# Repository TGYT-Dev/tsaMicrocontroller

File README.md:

a wearable project for TSA microcontroller project

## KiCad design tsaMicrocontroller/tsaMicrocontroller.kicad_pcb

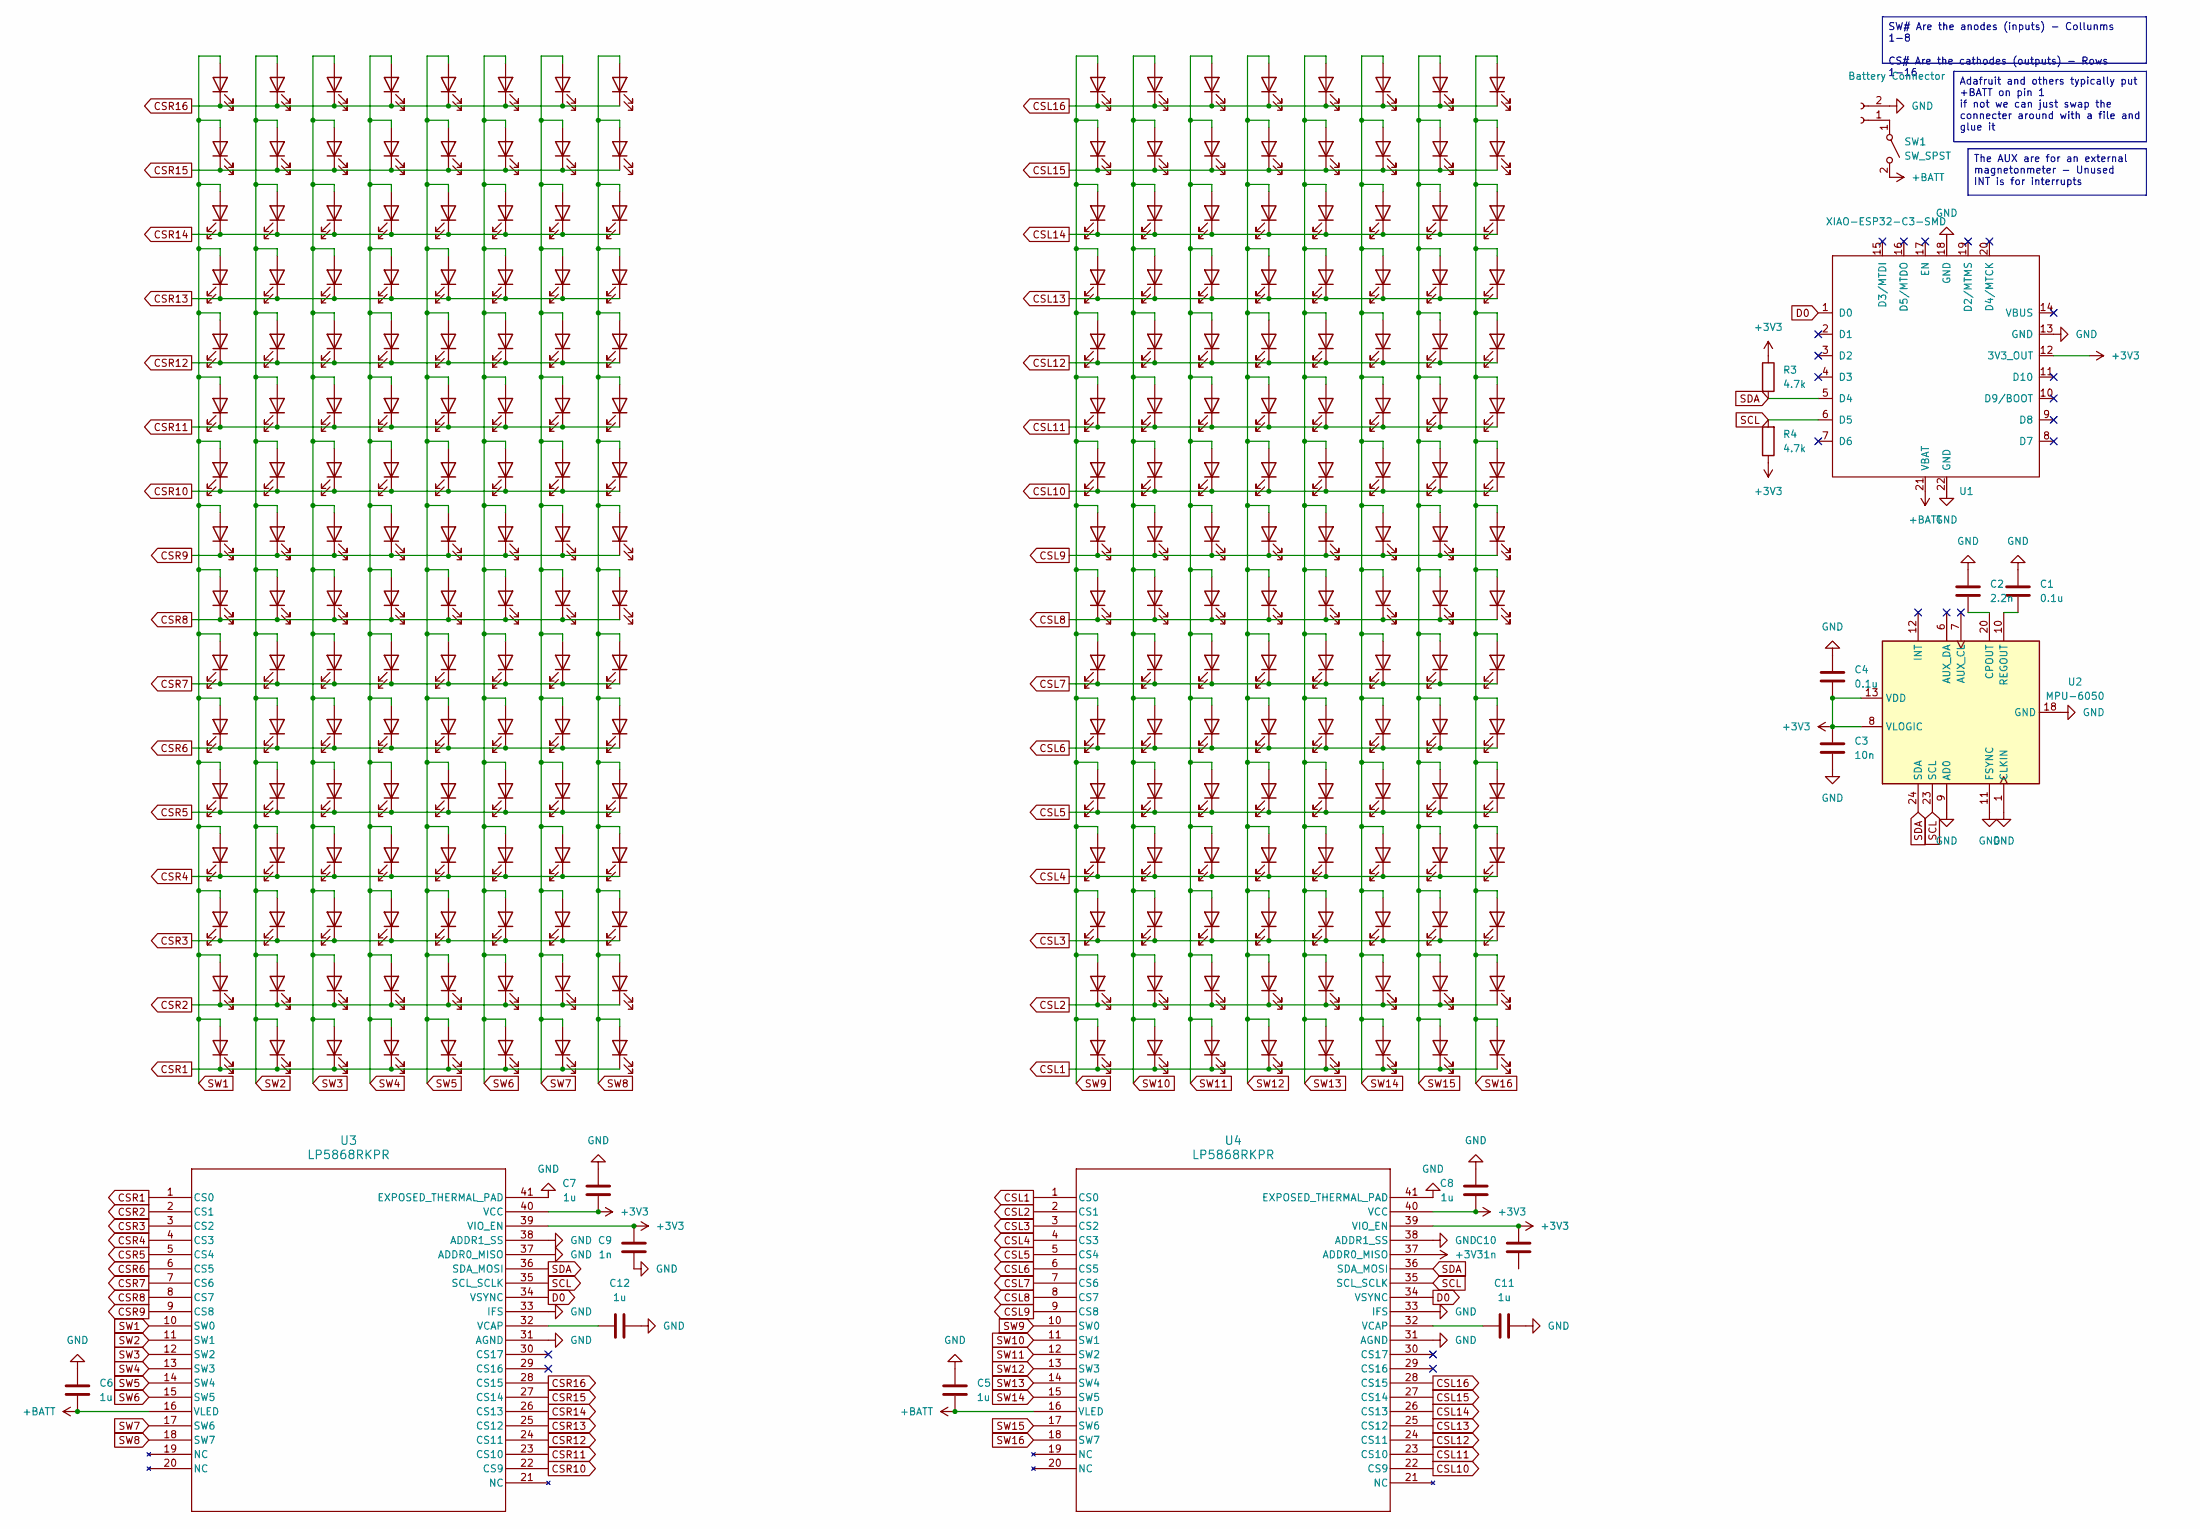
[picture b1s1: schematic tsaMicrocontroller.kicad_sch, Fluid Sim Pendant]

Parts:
C1, C4: 0.1u; C_01005_0402Metric
C2: 2.2n; C_01005_0402Metric
C3: 10n; C_01005_0402Metric
C5, C6, C7, C8, C11, C12: 1u; C_01005_0402Metric
C9, C10: 1n; C_01005_0402Metric
D146, D147, D148, D149, D150, D151, D152, D153, D154, D155, D156, D157, D158, D159, D160, D161, D162, D163, D164, D165, D166, D167, D168, D169, D170, D171, D172, D173, D174, D175, D176, D177, D178, D179, D180, D181, D182, D183, D184, D185, D186, D187, D188, D189, D190, D191, D192, D193, D194, D195, D196, D197, D198, D199, D200, D201, D202, D203, D204, D205, D206, D207, D208, D209, D210, D211, D212, D213, D214, D215, D216, D217, D218, D219, D220, D221, D222, D223, D224, D225, D226, D227, D228, D229, D230, D231, D232, D233, D234, D235, D236, D237, D238, D239, D240, D241, D242, D243, D244, D245, D246, D247, D248, D249, D250, D251, D252, D253, D254, D255, D256, D257, D258, D259, D260, D261, D262, D263, D264, D265, D266, D267, D268, D269, D270, D271, D272, D273, D274, D275, D276, D277, D278, D279, D280, D281, D282, D283, D284, D285, D286, D287, D288, D289, D290, D291, D292, D293, D294, D295, D296, D297, D298, D299, D300, D301, D302, D303, D304, D305, D306, D307, D308, D309, D310, D311, D312, D313, D314, D315, D316, D317, D318, D319, D320, D321, D322, D323, D324, D325, D326, D327, D328, D329, D330, D331, D332, D333, D334, D335, D336, D337, D338, D339, D340, D341, D342, D343, D344, D345, D346, D347, D348, D349, D350, D351, D352, D353, D354, D355, D356, D357, D358, D359, D360, D361, D362, D363, D364, D365, D366, D367, D368, D369, D370, D371, D372, D373, D374, D375, D376, D377, D378, D379, D380, D381, D382, D383, D384, D385, D386, D387, D388, D389, D390, D391, D392, D393, D394, D395, D396, D397, D398, D399, D400, D401: LED
J1: Battery Connector; JST_PH_S2B-PH-K_1x02_P2.00mm_Horizontal
R3, R4: 4.7k; R_0201_0603Metric_Pad0.64x0.40mm_HandSolder
SW1: SW_SPST; SW_DIP_SPSTx01_Slide_6.7x4.1mm_W6.73mm_P2.54mm_LowProfile_J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
U1: XIAO-ESP32-C3-SMD; MCU_Seeed_ESP32C3
U2: MPU-6050; InvenSense_QFN-24_4x4mm_P0.5mm
U3, U4: LP5868RKPR; VQFN40-RKP_TEX

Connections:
+3V3: C3.1, C4.2, C7.2, C8.2, C9.2, C10.2, R3.1, R4.1, U1.12 (3V3_OUT), U2.8 (VLOGIC), U2.13 (VDD), U3.39 (VIO_EN), U3.40 (VCC), U4.37 (ADDR0_MISO), U4.39 (VIO_EN), U4.40 (VCC)
+BATT: C5.2, C6.2, SW1.2 (B), U1.21 (VBAT), U3.16 (VLED), U4.16 (VLED)
CSL1: D279.1 (K), D301.1 (K), D321.1 (K), D337.1 (K), D353.1 (K), D369.1 (K), D385.1 (K), D401.1 (K), U4.1 (CS0)
CSL2: D276.1 (K), D300.1 (K), D320.1 (K), D336.1 (K), D352.1 (K), D368.1 (K), D384.1 (K), D400.1 (K), U4.2 (CS1)
CSL3: D275.1 (K), D297.1 (K), D319.1 (K), D335.1 (K), D351.1 (K), D367.1 (K), D383.1 (K), D399.1 (K), U4.3 (CS2)
CSL4: D274.1 (K), D296.1 (K), D318.1 (K), D334.1 (K), D350.1 (K), D366.1 (K), D382.1 (K), D398.1 (K), U4.4 (CS3)
CSL5: D273.1 (K), D295.1 (K), D317.1 (K), D333.1 (K), D349.1 (K), D365.1 (K), D381.1 (K), D397.1 (K), U4.5 (CS4)
CSL6: D272.1 (K), D294.1 (K), D316.1 (K), D332.1 (K), D348.1 (K), D364.1 (K), D380.1 (K), D396.1 (K), U4.6 (CS5)
CSL7: D241.1 (K), D293.1 (K), D315.1 (K), D331.1 (K), D347.1 (K), D363.1 (K), D379.1 (K), D395.1 (K), U4.7 (CS6)
CSL8: D240.1 (K), D290.1 (K), D314.1 (K), D330.1 (K), D346.1 (K), D362.1 (K), D378.1 (K), D394.1 (K), U4.8 (CS7)
CSL9: D225.1 (K), D289.1 (K), D311.1 (K), D329.1 (K), D345.1 (K), D361.1 (K), D377.1 (K), D393.1 (K), U4.9 (CS8)
CSL10: D192.1 (K), D288.1 (K), D310.1 (K), D328.1 (K), D344.1 (K), D360.1 (K), D376.1 (K), D392.1 (K), U4.22 (CS9)
CSL11: D177.1 (K), D287.1 (K), D309.1 (K), D327.1 (K), D343.1 (K), D359.1 (K), D375.1 (K), D391.1 (K), U4.23 (CS10)
CSL12: D176.1 (K), D286.1 (K), D308.1 (K), D326.1 (K), D342.1 (K), D358.1 (K), D374.1 (K), D390.1 (K), U4.24 (CS11)
CSL13: D161.1 (K), D283.1 (K), D307.1 (K), D325.1 (K), D341.1 (K), D357.1 (K), D373.1 (K), D389.1 (K), U4.25 (CS12)
CSL14: D160.1 (K), D282.1 (K), D304.1 (K), D324.1 (K), D340.1 (K), D356.1 (K), D372.1 (K), D388.1 (K), U4.26 (CS13)
CSL15: D224.1 (K), D281.1 (K), D303.1 (K), D323.1 (K), D339.1 (K), D355.1 (K), D371.1 (K), D387.1 (K), U4.27 (CS14)
CSL16: D209.1 (K), D280.1 (K), D302.1 (K), D322.1 (K), D338.1 (K), D354.1 (K), D370.1 (K), D386.1 (K), U4.28 (CS15)
CSR1: D152.1 (K), D168.1 (K), D184.1 (K), D200.1 (K), D216.1 (K), D232.1 (K), D248.1 (K), D264.1 (K), U3.1 (CS0)
CSR2: D151.1 (K), D167.1 (K), D183.1 (K), D199.1 (K), D215.1 (K), D231.1 (K), D247.1 (K), D263.1 (K), U3.2 (CS1)
CSR3: D150.1 (K), D166.1 (K), D182.1 (K), D198.1 (K), D214.1 (K), D230.1 (K), D246.1 (K), D262.1 (K), U3.3 (CS2)
CSR4: D149.1 (K), D165.1 (K), D181.1 (K), D197.1 (K), D213.1 (K), D229.1 (K), D245.1 (K), D261.1 (K), U3.4 (CS3)
CSR5: D148.1 (K), D164.1 (K), D180.1 (K), D196.1 (K), D212.1 (K), D228.1 (K), D244.1 (K), D260.1 (K), U3.5 (CS4)
CSR6: D147.1 (K), D163.1 (K), D179.1 (K), D195.1 (K), D211.1 (K), D227.1 (K), D243.1 (K), D259.1 (K), U3.6 (CS5)
CSR7: D146.1 (K), D162.1 (K), D178.1 (K), D194.1 (K), D210.1 (K), D226.1 (K), D242.1 (K), D258.1 (K), U3.7 (CS6)
CSR8: D159.1 (K), D175.1 (K), D191.1 (K), D207.1 (K), D223.1 (K), D239.1 (K), D255.1 (K), D271.1 (K), U3.8 (CS7)
CSR9: D158.1 (K), D174.1 (K), D190.1 (K), D206.1 (K), D222.1 (K), D238.1 (K), D254.1 (K), D270.1 (K), U3.9 (CS8)
CSR10: D157.1 (K), D173.1 (K), D189.1 (K), D205.1 (K), D221.1 (K), D237.1 (K), D253.1 (K), D269.1 (K), U3.22 (CS9)
CSR11: D156.1 (K), D172.1 (K), D188.1 (K), D204.1 (K), D220.1 (K), D236.1 (K), D252.1 (K), D268.1 (K), U3.23 (CS10)
CSR12: D155.1 (K), D171.1 (K), D187.1 (K), D203.1 (K), D219.1 (K), D235.1 (K), D251.1 (K), D267.1 (K), U3.24 (CS11)
CSR13: D154.1 (K), D170.1 (K), D186.1 (K), D202.1 (K), D218.1 (K), D234.1 (K), D250.1 (K), D266.1 (K), U3.25 (CS12)
CSR14: D153.1 (K), D169.1 (K), D185.1 (K), D201.1 (K), D217.1 (K), D233.1 (K), D249.1 (K), D265.1 (K), U3.26 (CS13)
CSR15: D208.1 (K), D257.1 (K), D278.1 (K), D285.1 (K), D292.1 (K), D299.1 (K), D306.1 (K), D313.1 (K), U3.27 (CS14)
CSR16: D193.1 (K), D256.1 (K), D277.1 (K), D284.1 (K), D291.1 (K), D298.1 (K), D305.1 (K), D312.1 (K), U3.28 (CS15)
D0: U1.1 (D0), U3.34 (VSYNC), U4.34 (VSYNC)
GND: C1.1, C2.1, C3.2, C4.1, C5.1, C6.1, C7.1, C8.1, C9.1, C11.1, C12.1, J1.2, U1.13 (GND), U1.18 (GND), U1.22 (GND), U2.1 (CLKIN), U2.9 (AD0), U2.11 (FSYNC), U2.18 (GND), U3.31 (AGND), U3.33 (IFS), U3.37 (ADDR0_MISO), U3.38 (ADDR1_SS), U3.41 (EXPOSED_THERMAL_PAD), U4.31 (AGND), U4.33 (IFS), U4.38 (ADDR1_SS), U4.41 (EXPOSED_THERMAL_PAD)
unnamed: J1.1, SW1.1 (A)
unnamed: C2.2, U2.20 (CPOUT)
unnamed: C1.2, U2.10 (REGOUT)
unnamed: C12.2, U3.32 (VCAP)
unnamed: C11.2, U4.32 (VCAP)
SCL: R4.2, U1.6 (D5), U2.23 (SCL), U3.35 (SCL_SCLK), U4.35 (SCL_SCLK)
SDA: R3.2, U1.5 (D4), U2.24 (SDA), U3.36 (SDA_MOSI), U4.36 (SDA_MOSI)
SW1: D146.2 (A), D147.2 (A), D148.2 (A), D149.2 (A), D150.2 (A), D151.2 (A), D152.2 (A), D153.2 (A), D154.2 (A), D155.2 (A), D156.2 (A), D157.2 (A), D158.2 (A), D159.2 (A), D193.2 (A), D208.2 (A), U3.10 (SW0)
SW2: D162.2 (A), D163.2 (A), D164.2 (A), D165.2 (A), D166.2 (A), D167.2 (A), D168.2 (A), D169.2 (A), D170.2 (A), D171.2 (A), D172.2 (A), D173.2 (A), D174.2 (A), D175.2 (A), D256.2 (A), D257.2 (A), U3.11 (SW1)
SW3: D178.2 (A), D179.2 (A), D180.2 (A), D181.2 (A), D182.2 (A), D183.2 (A), D184.2 (A), D185.2 (A), D186.2 (A), D187.2 (A), D188.2 (A), D189.2 (A), D190.2 (A), D191.2 (A), D277.2 (A), D278.2 (A), U3.12 (SW2)
SW4: D194.2 (A), D195.2 (A), D196.2 (A), D197.2 (A), D198.2 (A), D199.2 (A), D200.2 (A), D201.2 (A), D202.2 (A), D203.2 (A), D204.2 (A), D205.2 (A), D206.2 (A), D207.2 (A), D284.2 (A), D285.2 (A), U3.13 (SW3)
SW5: D210.2 (A), D211.2 (A), D212.2 (A), D213.2 (A), D214.2 (A), D215.2 (A), D216.2 (A), D217.2 (A), D218.2 (A), D219.2 (A), D220.2 (A), D221.2 (A), D222.2 (A), D223.2 (A), D291.2 (A), D292.2 (A), U3.14 (SW4)
SW6: D226.2 (A), D227.2 (A), D228.2 (A), D229.2 (A), D230.2 (A), D231.2 (A), D232.2 (A), D233.2 (A), D234.2 (A), D235.2 (A), D236.2 (A), D237.2 (A), D238.2 (A), D239.2 (A), D298.2 (A), D299.2 (A), U3.15 (SW5)
SW7: D242.2 (A), D243.2 (A), D244.2 (A), D245.2 (A), D246.2 (A), D247.2 (A), D248.2 (A), D249.2 (A), D250.2 (A), D251.2 (A), D252.2 (A), D253.2 (A), D254.2 (A), D255.2 (A), D305.2 (A), D306.2 (A), U3.17 (SW6)
SW8: D258.2 (A), D259.2 (A), D260.2 (A), D261.2 (A), D262.2 (A), D263.2 (A), D264.2 (A), D265.2 (A), D266.2 (A), D267.2 (A), D268.2 (A), D269.2 (A), D270.2 (A), D271.2 (A), D312.2 (A), D313.2 (A), U3.18 (SW7)
SW9: D160.2 (A), D161.2 (A), D176.2 (A), D177.2 (A), D192.2 (A), D209.2 (A), D224.2 (A), D225.2 (A), D240.2 (A), D241.2 (A), D272.2 (A), D273.2 (A), D274.2 (A), D275.2 (A), D276.2 (A), D279.2 (A), U4.10 (SW0)
SW10: D280.2 (A), D281.2 (A), D282.2 (A), D283.2 (A), D286.2 (A), D287.2 (A), D288.2 (A), D289.2 (A), D290.2 (A), D293.2 (A), D294.2 (A), D295.2 (A), D296.2 (A), D297.2 (A), D300.2 (A), D301.2 (A), U4.11 (SW1)
SW11: D302.2 (A), D303.2 (A), D304.2 (A), D307.2 (A), D308.2 (A), D309.2 (A), D310.2 (A), D311.2 (A), D314.2 (A), D315.2 (A), D316.2 (A), D317.2 (A), D318.2 (A), D319.2 (A), D320.2 (A), D321.2 (A), U4.12 (SW2)
SW12: D322.2 (A), D323.2 (A), D324.2 (A), D325.2 (A), D326.2 (A), D327.2 (A), D328.2 (A), D329.2 (A), D330.2 (A), D331.2 (A), D332.2 (A), D333.2 (A), D334.2 (A), D335.2 (A), D336.2 (A), D337.2 (A), U4.13 (SW3)
SW13: D338.2 (A), D339.2 (A), D340.2 (A), D341.2 (A), D342.2 (A), D343.2 (A), D344.2 (A), D345.2 (A), D346.2 (A), D347.2 (A), D348.2 (A), D349.2 (A), D350.2 (A), D351.2 (A), D352.2 (A), D353.2 (A), U4.14 (SW4)
SW14: D354.2 (A), D355.2 (A), D356.2 (A), D357.2 (A), D358.2 (A), D359.2 (A), D360.2 (A), D361.2 (A), D362.2 (A), D363.2 (A), D364.2 (A), D365.2 (A), D366.2 (A), D367.2 (A), D368.2 (A), D369.2 (A), U4.15 (SW5)
SW15: D370.2 (A), D371.2 (A), D372.2 (A), D373.2 (A), D374.2 (A), D375.2 (A), D376.2 (A), D377.2 (A), D378.2 (A), D379.2 (A), D380.2 (A), D381.2 (A), D382.2 (A), D383.2 (A), D384.2 (A), D385.2 (A), U4.17 (SW6)
SW16: D386.2 (A), D387.2 (A), D388.2 (A), D389.2 (A), D390.2 (A), D391.2 (A), D392.2 (A), D393.2 (A), D394.2 (A), D395.2 (A), D396.2 (A), D397.2 (A), D398.2 (A), D399.2 (A), D400.2 (A), D401.2 (A), U4.18 (SW7)

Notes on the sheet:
The AUX are for an external magnetonmeter - Unused INT is for interrupts
SW# Are the anodes (inputs) - Collunms 1-8 CS# Are the cathodes (outputs) - Rows 1-16
Adafruit and others typically put +BATT on pin 1 if not we can just swap the connecter around with a file and glue it

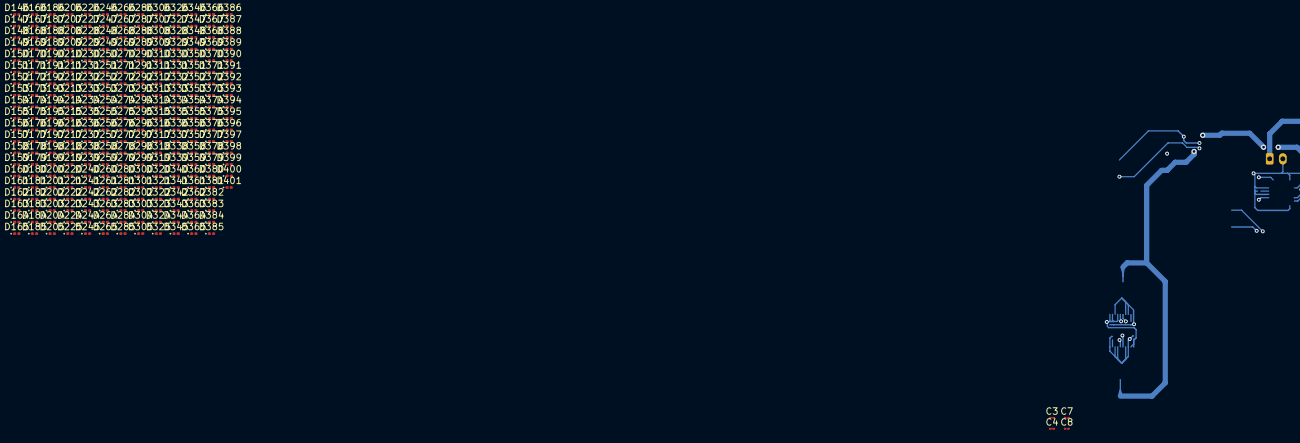
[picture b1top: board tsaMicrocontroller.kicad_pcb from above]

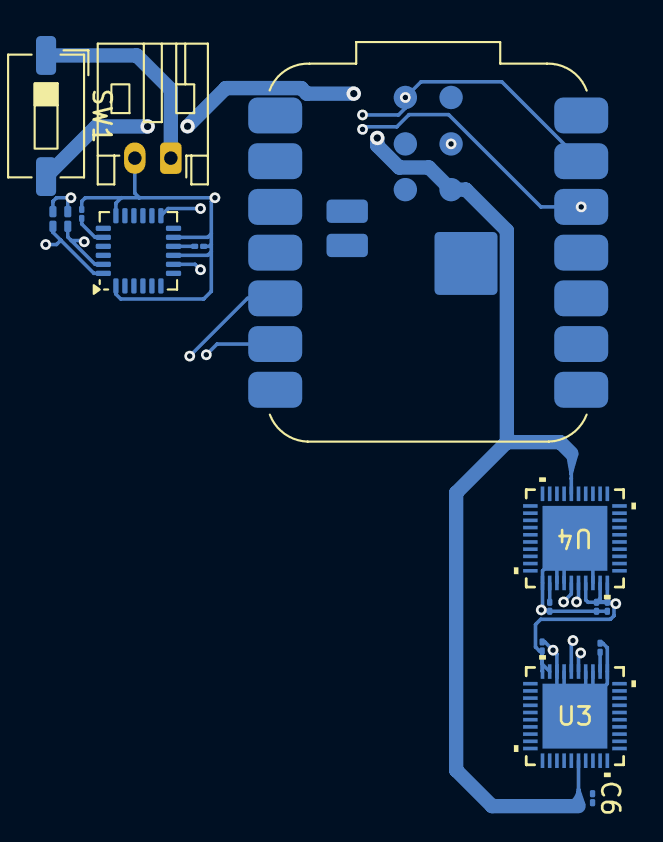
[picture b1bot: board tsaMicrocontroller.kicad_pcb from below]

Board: 4 copper layers, 276 parts (16 on the bottom side), 59 nets.
